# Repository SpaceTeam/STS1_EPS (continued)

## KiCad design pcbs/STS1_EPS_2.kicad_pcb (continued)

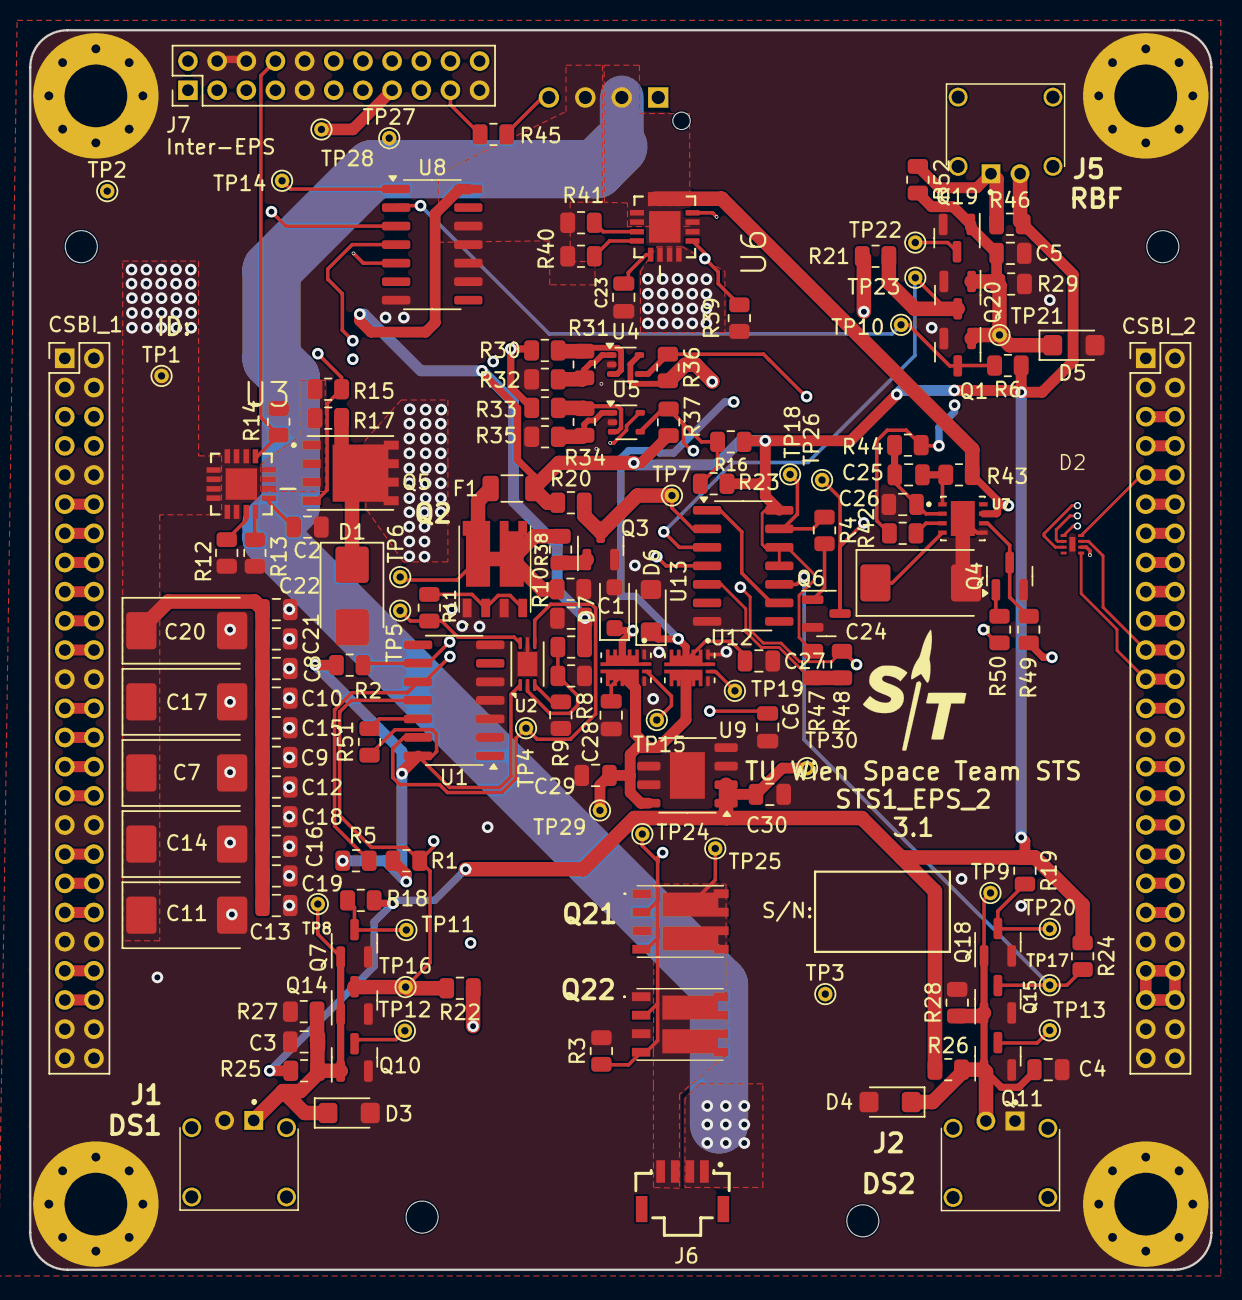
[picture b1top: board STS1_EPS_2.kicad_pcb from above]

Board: 6 copper layers, 81.0 x 85.0 mm, 164 parts (1 on the bottom side), 95 nets.

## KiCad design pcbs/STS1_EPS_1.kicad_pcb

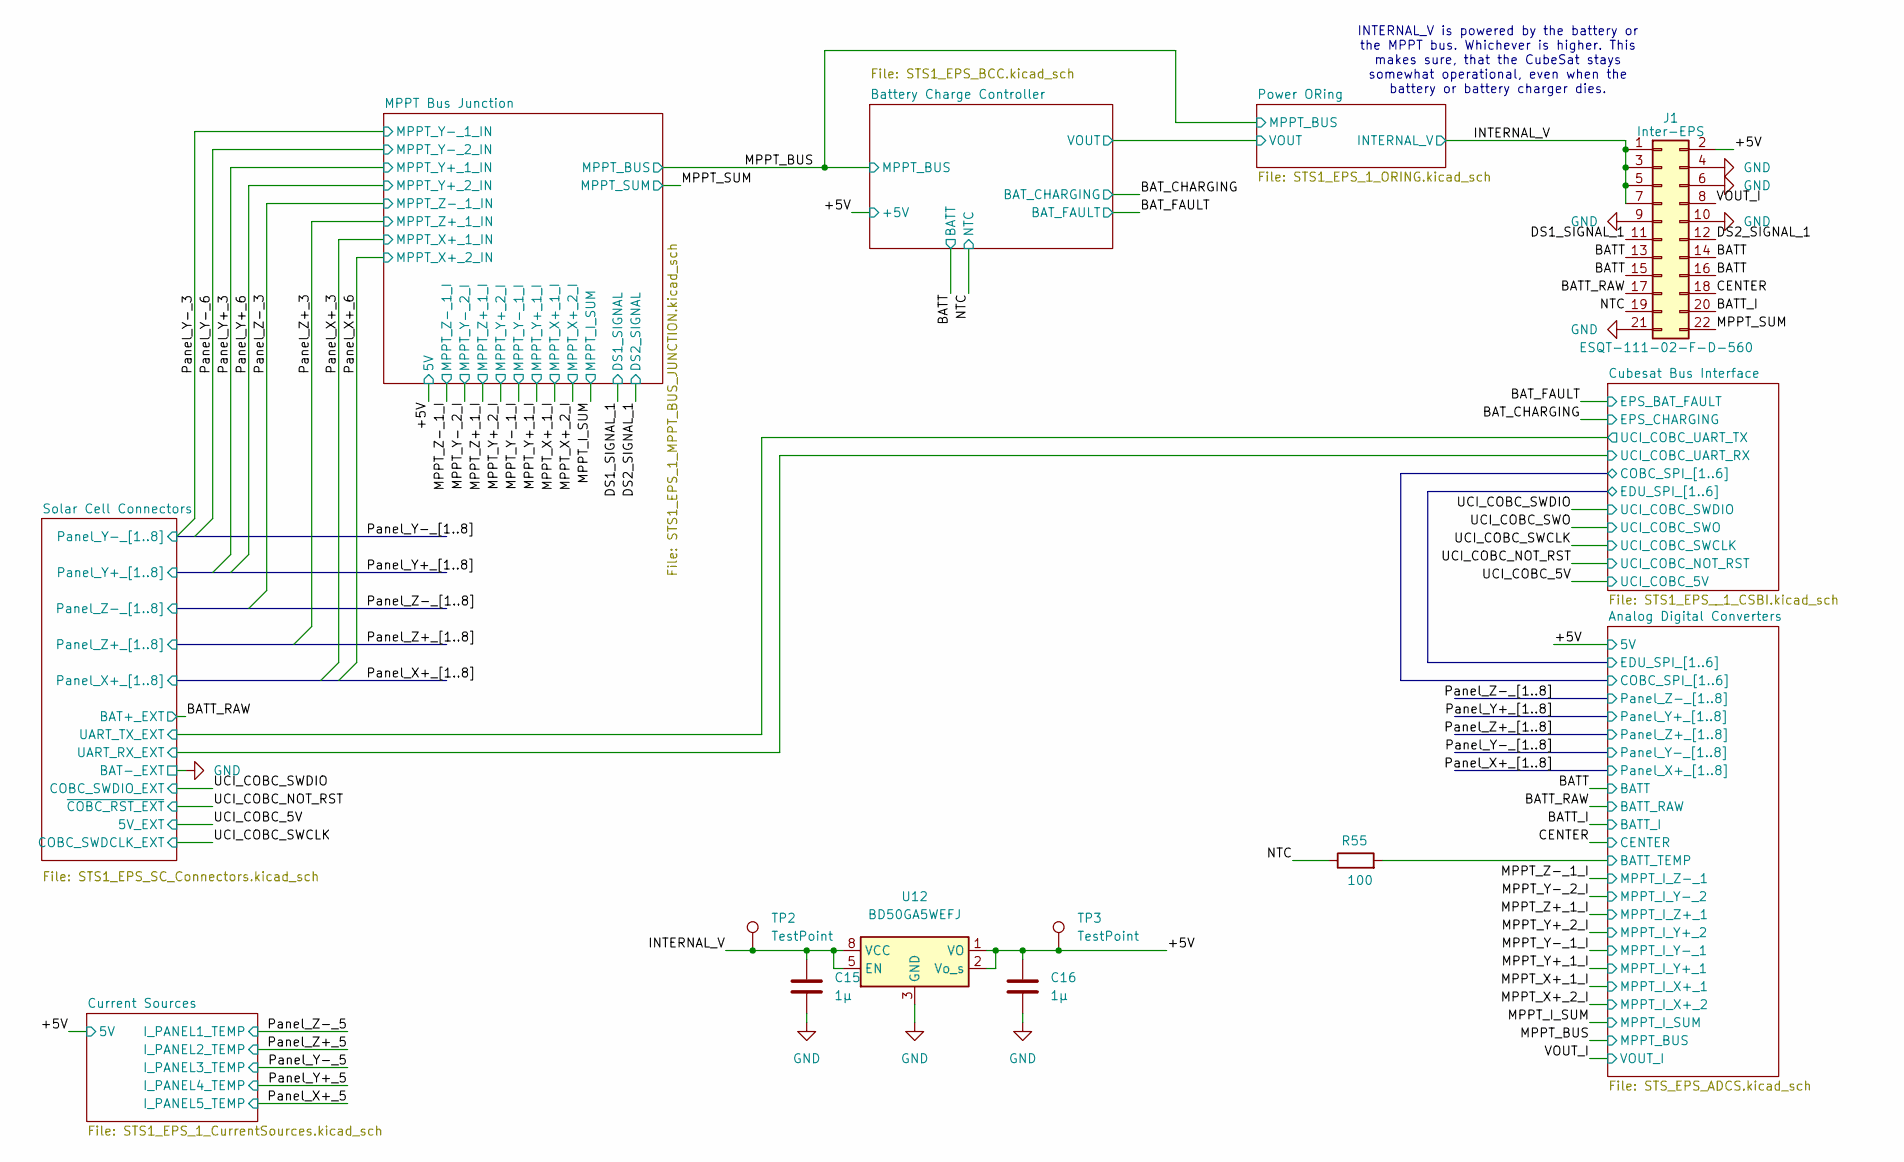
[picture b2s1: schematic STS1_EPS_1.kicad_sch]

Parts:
C15, C16: 1µ; C_0805_2012Metric; Part Nr. C0805T105K4RALTU
J1: Inter-EPS; PinHeader_2x11_P2.00mm_Vertical; Part# ESQT-111-02-F-D-560
R55: 100; R_0805_2012Metric; Part Nr. TNPW0805100RFETA
TP2, TP3: TestPoint; TestPoint_THTPad_D1.0mm_Drill0.5mm
U12: BD50GA5WEFJ; HTSOP-8-1EP_3.9x4.9mm_P1.27mm_EP2.4x3.2mm

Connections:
/+5V: C16.1, J1.2, TP3.1 (1_1), U12.1 (VO), U12.2 (Vo_s); also elsewhere on the board
/Analog Digital Converters/BATT_TEMP: R55.2; also elsewhere on the board
/BATT: J1.13, J1.14, J1.15, J1.16; also elsewhere on the board
/BATT_I: J1.20; also elsewhere on the board
/BATT_RAW: J1.17; also elsewhere on the board
/CENTER: J1.18; also elsewhere on the board
/DS1_SIGNAL_1: J1.11; also elsewhere on the board
/DS2_SIGNAL_1: J1.12; also elsewhere on the board
/INTERNAL_V: C15.1, J1.1, J1.3, J1.5, J1.7, TP2.1 (1_1), U12.5 (EN), U12.8 (VCC); also elsewhere on the board
/NTC: J1.19, R55.1; also elsewhere on the board
/VOUT_I: J1.8; also elsewhere on the board
GND: C15.2, C16.2, J1.4, J1.6, J1.9, J1.10, J1.21, U12.3 (GND), U12.4 (GND), U12.6 (GND), U12.7 (GND), U12.9 (GND); also elsewhere on the board

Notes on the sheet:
INTERNAL_V is powered by the battery or the MPPT bus. Whichever is higher. This makes sure, that the CubeSat stays somewhat operational, even when the battery or battery charger dies.

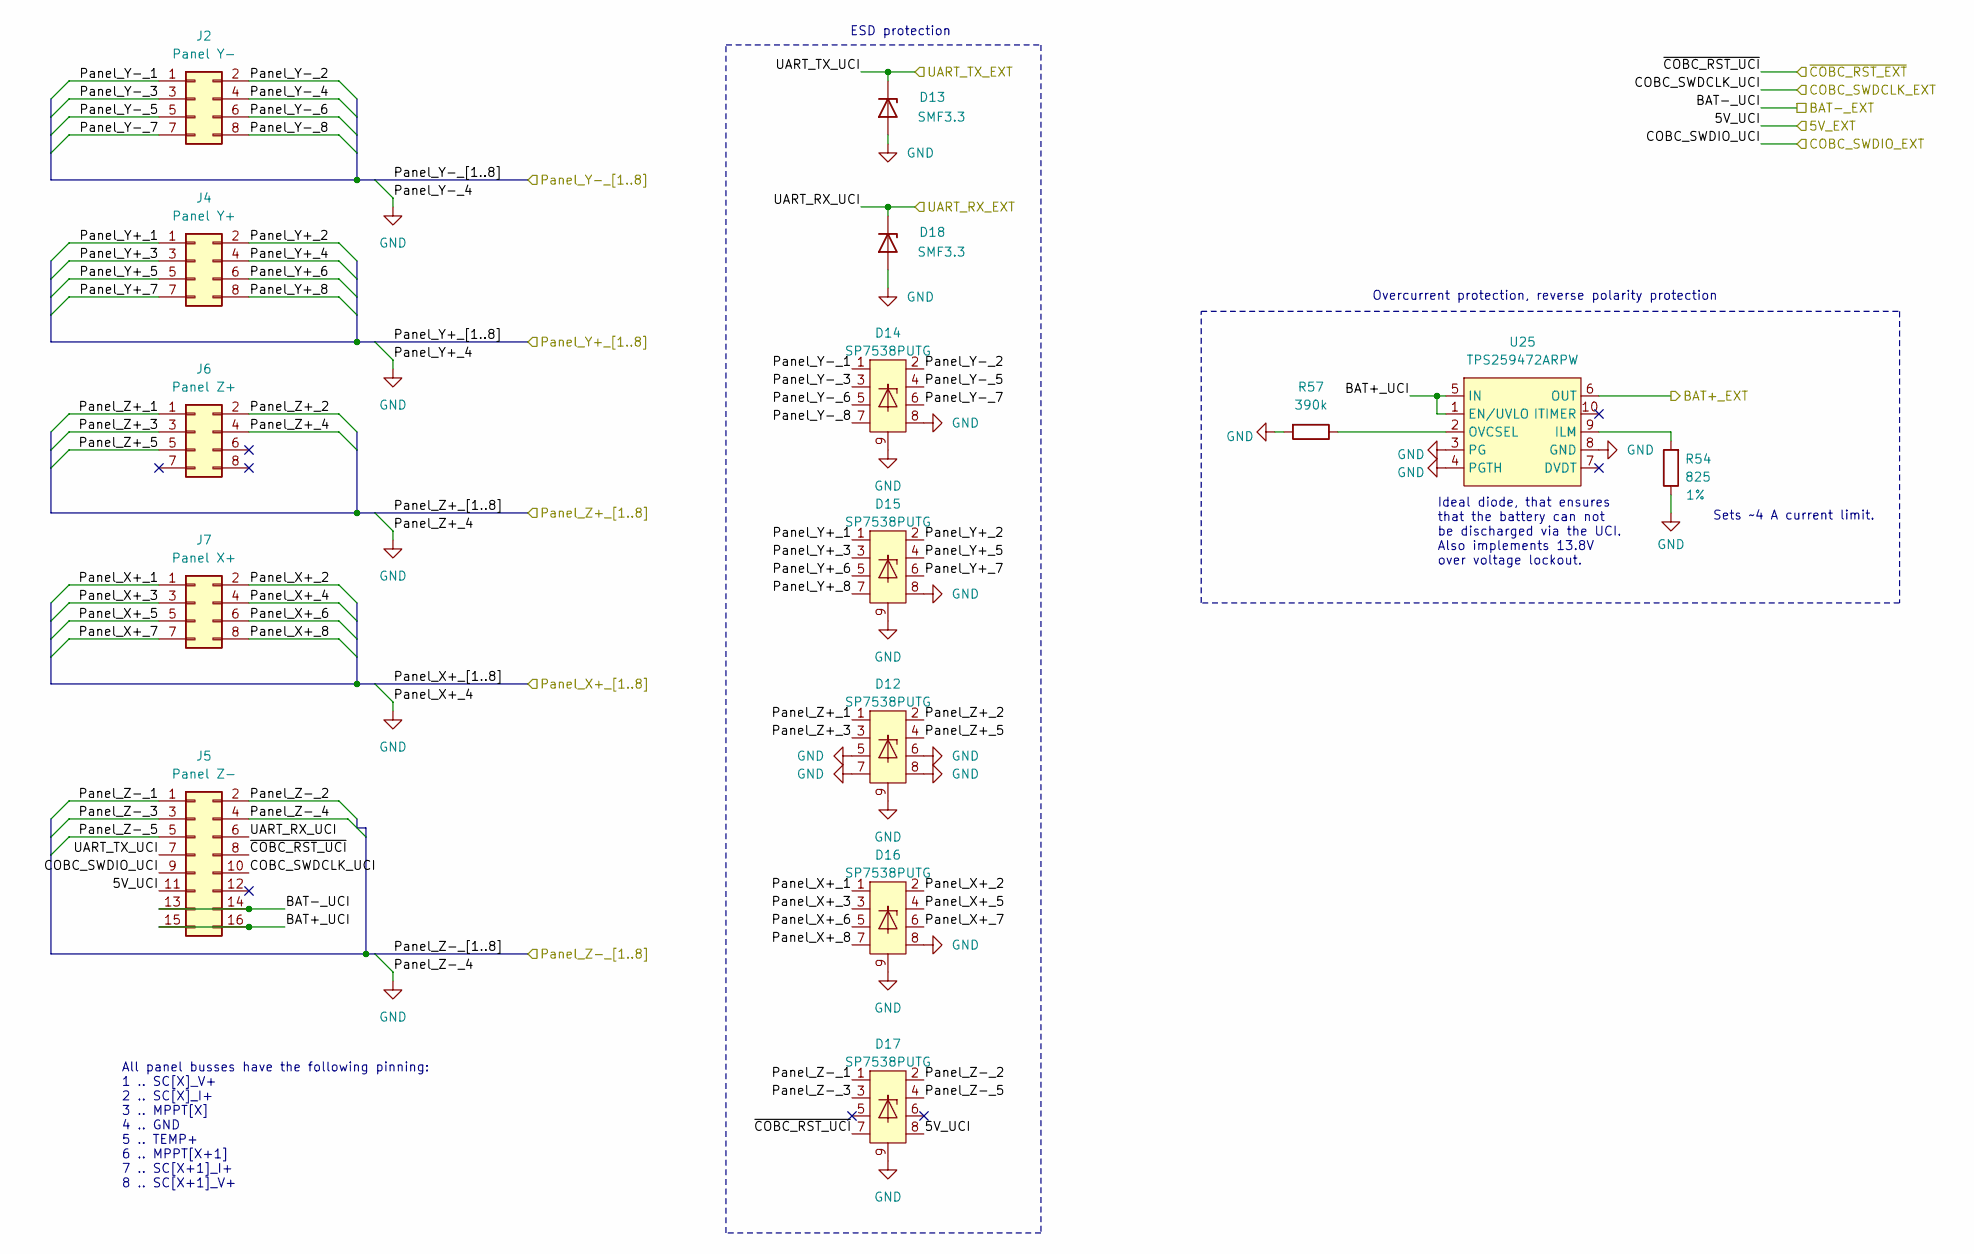
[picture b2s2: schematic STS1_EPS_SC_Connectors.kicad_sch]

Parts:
D12, D14, D15, D16, D17: SP7538PUTG; Diodes_UDFN3810-9_TYPE_B
D13, D18: SMF3.3; D_SOD-123; Part Nr. SMF3.3
J2: Panel Y-; Samtec_T1M-08-X-SV-L_1x08-1MP_P1.0mm_Terminal_Vertical_Latch; Part Nr. SAMTEC_ZF5S-08-03-T-WT
J4: Panel Y+; Samtec_T1M-08-X-SV-L_1x08-1MP_P1.0mm_Terminal_Vertical_Latch; Part Nr. SAMTEC_ZF5S-08-03-T-WT
J5: Panel Z-; Samtec_T1M-16-X-SV-L_1x16-1MP_P1.0mm_Terminal_Vertical_Latch; Part Nr. SAMTEC_ZF5S-08-03-T-WT
J6: Panel Z+; Samtec_T1M-08-X-SV-L_1x08-1MP_P1.0mm_Terminal_Vertical_Latch; Part Nr. SAMTEC_ZF5S-08-03-T-WT
J7: Panel X+; Samtec_T1M-08-X-SV-L_1x08-1MP_P1.0mm_Terminal_Vertical_Latch; Part Nr. SAMTEC_ZF5S-08-03-T-WT
R54: 825; R_0805_2012Metric; Tolerance 1%; Part Nr. RT0805FRE07825RL
R57: 390k; R_0805_2012Metric; Part Nr. RN73R2ATTD3903F25
U25: TPS259472ARPW; TPS259472ARPWR

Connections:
/BATT_RAW: U25.6 (OUT); also elsewhere on the board
/Panel_X+_1: D16.1, J7.1; also elsewhere on the board
/Panel_X+_2: D16.2, J7.2; also elsewhere on the board
/Panel_X+_3: D16.3, J7.3; also elsewhere on the board
/Panel_X+_5: D16.4, J7.5; also elsewhere on the board
/Panel_X+_6: D16.5, J7.6; also elsewhere on the board
/Panel_X+_7: D16.6, J7.7; also elsewhere on the board
/Panel_X+_8: D16.7, J7.8; also elsewhere on the board
/Panel_Y+_1: D15.1, J4.1; also elsewhere on the board
/Panel_Y+_2: D15.2, J4.2; also elsewhere on the board
/Panel_Y+_3: D15.3, J4.3; also elsewhere on the board
/Panel_Y+_5: D15.4, J4.5; also elsewhere on the board
/Panel_Y+_6: D15.5, J4.6; also elsewhere on the board
/Panel_Y+_7: D15.6, J4.7; also elsewhere on the board
/Panel_Y+_8: D15.7, J4.8; also elsewhere on the board
/Panel_Y-_1: D14.1, J2.1; also elsewhere on the board
/Panel_Y-_2: D14.2, J2.2; also elsewhere on the board
/Panel_Y-_3: D14.3, J2.3; also elsewhere on the board
/Panel_Y-_5: D14.4, J2.5; also elsewhere on the board
/Panel_Y-_6: D14.5, J2.6; also elsewhere on the board
/Panel_Y-_7: D14.6, J2.7; also elsewhere on the board
/Panel_Y-_8: D14.7, J2.8; also elsewhere on the board
/Panel_Z+_1: D12.1, J6.1; also elsewhere on the board
/Panel_Z+_2: D12.2, J6.2; also elsewhere on the board
/Panel_Z+_3: D12.3, J6.3; also elsewhere on the board
/Panel_Z+_5: D12.4, J6.5; also elsewhere on the board
/Panel_Z-_1: D17.1, J5.1; also elsewhere on the board
/Panel_Z-_2: D17.2, J5.2; also elsewhere on the board
/Panel_Z-_3: D17.3, J5.3; also elsewhere on the board
/Panel_Z-_5: D17.4, J5.5; also elsewhere on the board
/Solar Cell Connectors/BAT+_UCI: J5.15, J5.16, U25.1 (EN/UVLO), U25.5 (IN)
/Solar Cell Connectors/UART_RX_UCI: D18.1 (K), J5.6; also elsewhere on the board
/Solar Cell Connectors/UART_TX_UCI: D13.1 (K), J5.7; also elsewhere on the board
/UCI_COBC_5V: D17.8, J5.11; also elsewhere on the board
/UCI_COBC_NOT_RST: D17.7, J5.8; also elsewhere on the board
/UCI_COBC_SWCLK: J5.10; also elsewhere on the board
/UCI_COBC_SWDIO: J5.9; also elsewhere on the board
GND: D12.5, D12.6, D12.7, D12.8, D12.9, D13.2 (A), D14.8, D14.9, D15.8, D15.9, D16.8, D16.9, D17.9, D18.2 (A), J2.4, J4.4, J5.4, J5.13, J5.14, J6.4, J7.4, R54.1, R57.2, U25.3 (PG), U25.4 (PGTH), U25.8 (GND); also elsewhere on the board
unnamed: R54.2, U25.9 (ILM)
unnamed: R57.1, U25.2 (OVCSEL)

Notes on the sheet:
ESD protection
Overcurrent protection, reverse polarity protection
Sets ~4 A current limit.
Ideal diode, that ensures that the battery can not be discharged via the UCI. Also implements 13.8V over voltage lockout.
All panel busses have the following pinning: 1 .. SC[X]_V+ 2 .. SC[X]_I+ 3 .. MPPT[X] 4 .. GND 5 .. TEMP+ 6 .. MPPT[X+1] 7 .. SC[X+1]_I+ 8 .. SC[X+1]_V+

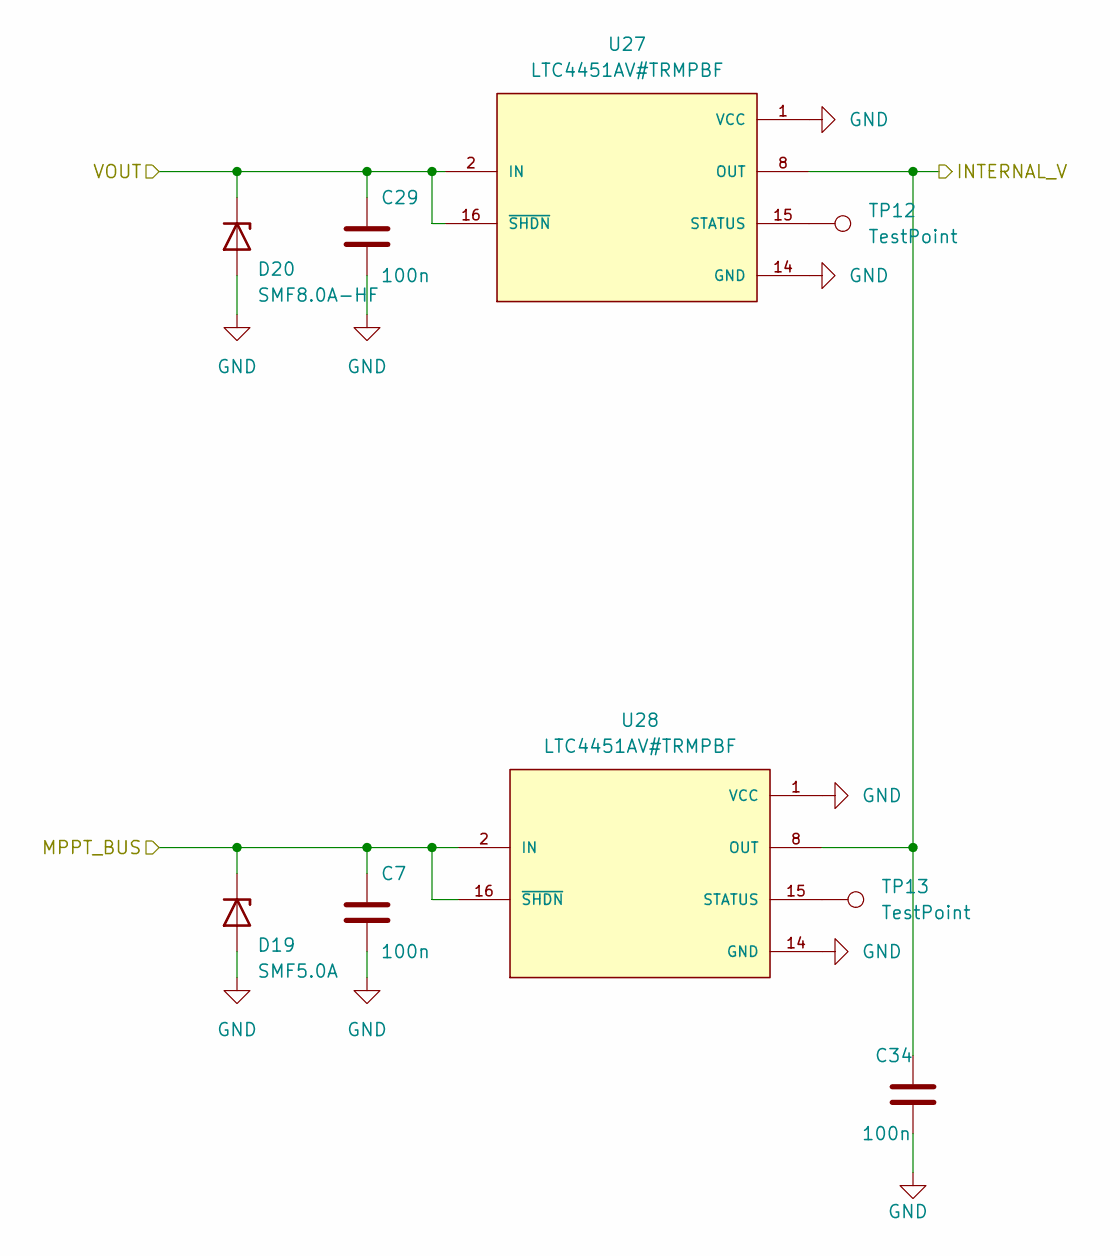
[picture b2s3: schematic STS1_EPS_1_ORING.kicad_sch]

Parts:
C7, C29, C34: 100n; C_0805_2012Metric; Part Nr. C0805T104K1RCLTU
D19: SMF5.0A; D_SMF; Part Nr. SMF5.0A
D20: SMF8.0A-HF; D_SOD-123F; Part Nr. SMF8.0A-HF
TP12, TP13: TestPoint; TestPoint_THTPad_D1.0mm_Drill0.5mm
U27, U28: LTC4451AV#TRMPBF; AD_LQFN-16; PARTREV 0

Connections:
/Battery Charge Controller/VOUT: C29.1, D20.1 (K), U27.2 (IN), U27.16 (~SHDN); also elsewhere on the board
/INTERNAL_V: C34.1, U27.8 (OUT), U28.8 (OUT); also elsewhere on the board
/MPPT_BUS: C7.1, D19.1 (K), U28.2 (IN), U28.16 (~SHDN); also elsewhere on the board
GND: C7.2, C29.2, C34.2, D19.2 (A), D20.2 (A), U27.1 (VCC), U27.14 (GND), U28.1 (VCC), U28.14 (GND); also elsewhere on the board
unnamed: TP12.1 (1_1), U27.15 (STATUS)
unnamed: TP13.1 (1_1), U28.15 (STATUS)

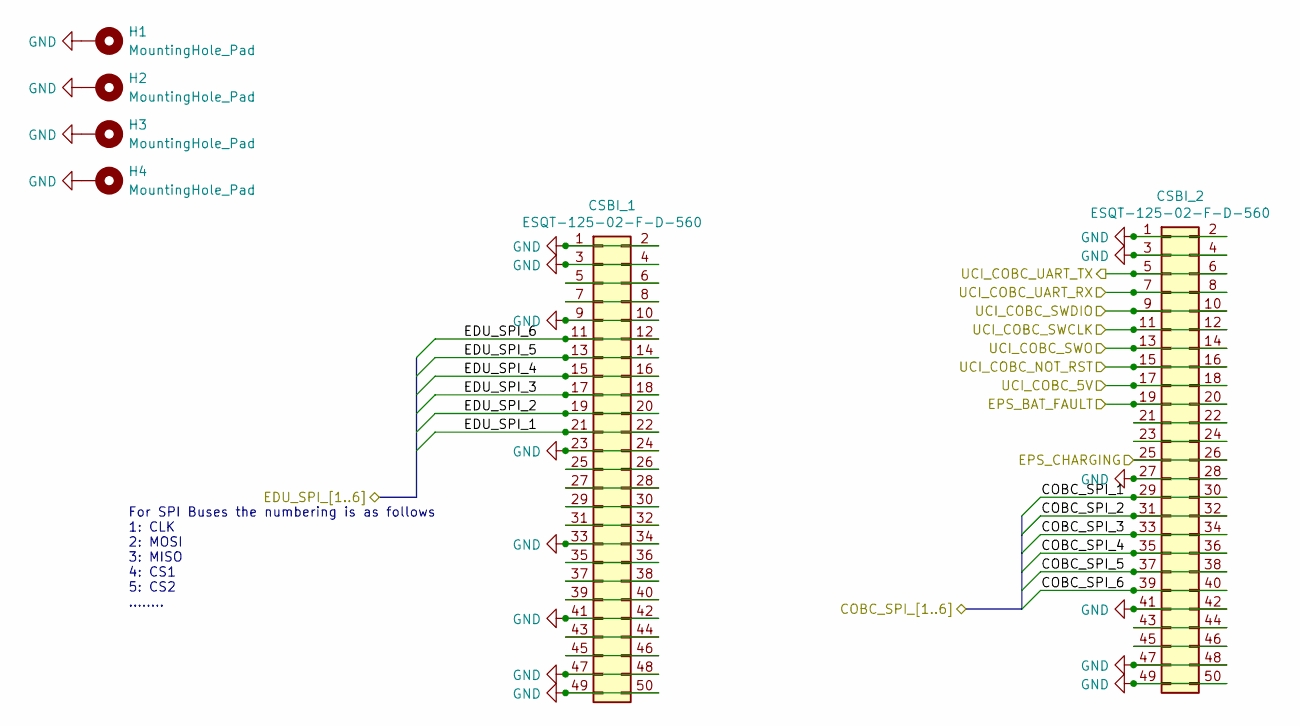
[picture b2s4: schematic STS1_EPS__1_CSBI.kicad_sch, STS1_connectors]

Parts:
CSBI_1, CSBI_2: ESQT-125-02-F-D-560; PinHeader_2x25_P2.00mm_Vertical; Part# ESQT-125-02-F-D-800
H1, H2, H3, H4: MountingHole_Pad; MountingHole_4.3mm_M4_Pad_Via

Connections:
/Analog Digital Converters/COBC_SPI_1: CSBI_2.29, CSBI_2.30; also elsewhere on the board
/Analog Digital Converters/COBC_SPI_2: CSBI_2.31, CSBI_2.32; also elsewhere on the board
/Analog Digital Converters/COBC_SPI_3: CSBI_2.33, CSBI_2.34; also elsewhere on the board
/Analog Digital Converters/COBC_SPI_4: CSBI_2.35, CSBI_2.36; also elsewhere on the board
/Analog Digital Converters/COBC_SPI_5: CSBI_2.37, CSBI_2.38; also elsewhere on the board
/Analog Digital Converters/COBC_SPI_6: CSBI_2.39, CSBI_2.40; also elsewhere on the board
/Analog Digital Converters/EDU_SPI_1: CSBI_1.21, CSBI_1.22; also elsewhere on the board
/Analog Digital Converters/EDU_SPI_2: CSBI_1.19, CSBI_1.20; also elsewhere on the board
/Analog Digital Converters/EDU_SPI_3: CSBI_1.17, CSBI_1.18; also elsewhere on the board
/Analog Digital Converters/EDU_SPI_4: CSBI_1.15, CSBI_1.16; also elsewhere on the board
/Analog Digital Converters/EDU_SPI_5: CSBI_1.13, CSBI_1.14; also elsewhere on the board
/Analog Digital Converters/EDU_SPI_6: CSBI_1.11, CSBI_1.12; also elsewhere on the board
/BAT_CHARGING: CSBI_2.25, CSBI_2.26; also elsewhere on the board
/BAT_FAULT: CSBI_2.19, CSBI_2.20; also elsewhere on the board
/Solar Cell Connectors/UART_RX_UCI: CSBI_2.7, CSBI_2.8; also elsewhere on the board
/Solar Cell Connectors/UART_TX_UCI: CSBI_2.5, CSBI_2.6; also elsewhere on the board
/UCI_COBC_5V: CSBI_2.17, CSBI_2.18; also elsewhere on the board
/UCI_COBC_NOT_RST: CSBI_2.15, CSBI_2.16; also elsewhere on the board
/UCI_COBC_SWCLK: CSBI_2.11, CSBI_2.12; also elsewhere on the board
/UCI_COBC_SWDIO: CSBI_2.9, CSBI_2.10; also elsewhere on the board
/UCI_COBC_SWO: CSBI_2.13, CSBI_2.14
GND: CSBI_1.1, CSBI_1.2, CSBI_1.3, CSBI_1.4, CSBI_1.9, CSBI_1.10, CSBI_1.23, CSBI_1.24, CSBI_1.33, CSBI_1.34, CSBI_1.41, CSBI_1.42, CSBI_1.47, CSBI_1.48, CSBI_1.49, CSBI_1.50, CSBI_2.1, CSBI_2.2, CSBI_2.3, CSBI_2.4, CSBI_2.27, CSBI_2.28, CSBI_2.41, CSBI_2.42, CSBI_2.47, CSBI_2.48, CSBI_2.49, CSBI_2.50, H1.1 (1_1), H2.1 (1_1), H3.1 (1_1), H4.1 (1_1); also elsewhere on the board
unnamed: CSBI_1.5, CSBI_1.6
unnamed: CSBI_1.7, CSBI_1.8
unnamed: CSBI_1.25, CSBI_1.26
unnamed: CSBI_1.27, CSBI_1.28
unnamed: CSBI_1.29, CSBI_1.30
unnamed: CSBI_1.31, CSBI_1.32
unnamed: CSBI_1.35, CSBI_1.36
unnamed: CSBI_1.37, CSBI_1.38
unnamed: CSBI_1.39, CSBI_1.40
unnamed: CSBI_1.43, CSBI_1.44
unnamed: CSBI_1.45, CSBI_1.46
unnamed: CSBI_2.21, CSBI_2.22
unnamed: CSBI_2.23, CSBI_2.24
unnamed: CSBI_2.43, CSBI_2.44
unnamed: CSBI_2.45, CSBI_2.46

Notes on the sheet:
For SPI Buses the numbering is as follows 1: CLK 2: MOSI 3: MISO 4: CS1 5: CS2 ........

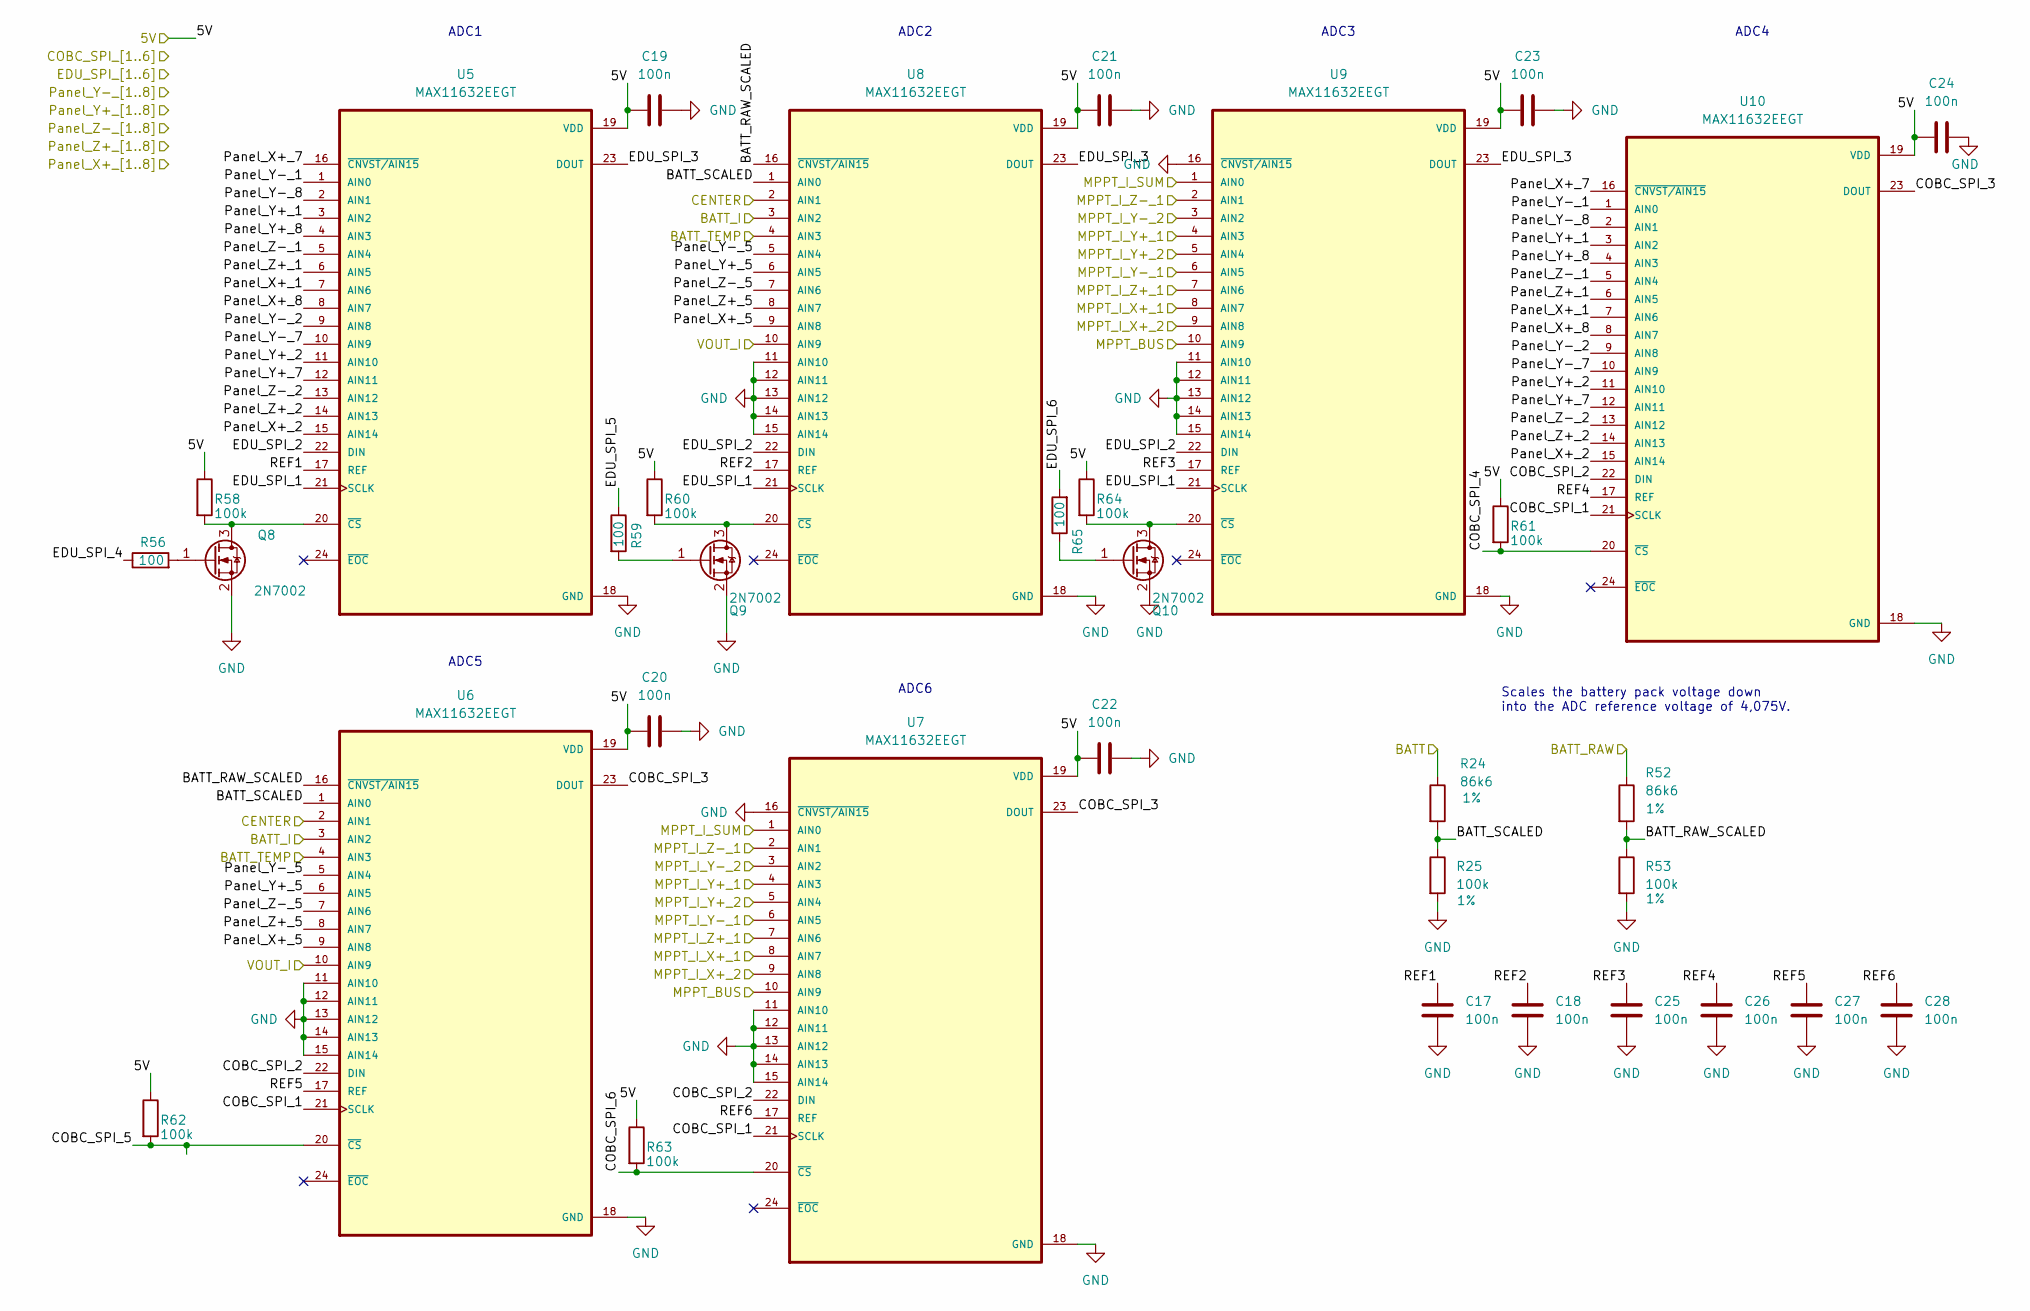
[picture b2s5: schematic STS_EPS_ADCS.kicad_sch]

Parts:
C17, C18, C19, C20, C21, C22, C23, C24, C25, C26, C27, C28: 100n; C_0805_2012Metric; Part Nr. C0805T104K1RCLTU
Q8, Q9, Q10: 2N7002; SOT-23; Part Nr. 2N7002
R24, R52: 86k6; R_0805_2012Metric; Tolerance 1%; Part Nr. RCA080586K6FKEA
R25, R53: 100k; R_0805_2012Metric; Tolerance 1%; Part Nr. TNPW0805100KFEEA
R56, R59, R65: 100; R_0805_2012Metric; Part Nr. TNPW0805100RFETA
R58, R60, R61, R62, R63, R64: 100k; R_0805_2012Metric; Part Nr. TNPW0805100KFEEA
U5, U6, U7, U8, U9, U10: MAX11632EEGT; MAX_QSOP24

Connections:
/+5V: C19.1, C20.1, C21.1, C22.1, C23.1, C24.1, R58.1, R60.1, R61.1, R62.1, R63.1, R64.1, U5.19 (VDD), U6.19 (VDD), U7.19 (VDD), U8.19 (VDD), U9.19 (VDD), U10.19 (VDD); also elsewhere on the board
/Analog Digital Converters/BATT_RAW_SCALED: R52.2, R53.1, U6.16 (~CNVST/AIN15), U8.16 (~CNVST/AIN15)
/Analog Digital Converters/BATT_SCALED: R24.2, R25.1, U6.1 (AIN0), U8.1 (AIN0)
/Analog Digital Converters/BATT_TEMP: U6.4 (AIN3), U8.4 (AIN3); also elsewhere on the board
/Analog Digital Converters/COBC_SPI_1: U6.21 (SCLK), U7.21 (SCLK), U10.21 (SCLK); also elsewhere on the board
/Analog Digital Converters/COBC_SPI_2: U6.22 (DIN), U7.22 (DIN), U10.22 (DIN); also elsewhere on the board
/Analog Digital Converters/COBC_SPI_3: U6.23 (DOUT), U7.23 (DOUT), U10.23 (DOUT); also elsewhere on the board
/Analog Digital Converters/COBC_SPI_4: R61.2, U10.20 (~CS); also elsewhere on the board
/Analog Digital Converters/COBC_SPI_5: R62.2, U6.20 (~CS); also elsewhere on the board
/Analog Digital Converters/COBC_SPI_6: R63.2, U7.20 (~CS); also elsewhere on the board
/Analog Digital Converters/EDU_SPI_1: U5.21 (SCLK), U8.21 (SCLK), U9.21 (SCLK); also elsewhere on the board
/Analog Digital Converters/EDU_SPI_2: U5.22 (DIN), U8.22 (DIN), U9.22 (DIN); also elsewhere on the board
/Analog Digital Converters/EDU_SPI_3: U5.23 (DOUT), U8.23 (DOUT), U9.23 (DOUT); also elsewhere on the board
/Analog Digital Converters/EDU_SPI_4: R56.1; also elsewhere on the board
/Analog Digital Converters/EDU_SPI_5: R59.1; also elsewhere on the board
/Analog Digital Converters/EDU_SPI_6: R65.2; also elsewhere on the board
/Analog Digital Converters/REF1: C17.2, U5.17 (REF)
/Analog Digital Converters/REF2: C18.2, U8.17 (REF)
/Analog Digital Converters/REF3: C25.2, U9.17 (REF)
/Analog Digital Converters/REF4: C26.2, U10.17 (REF)
/Analog Digital Converters/REF5: C27.2, U6.17 (REF)
/Analog Digital Converters/REF6: C28.2, U7.17 (REF)
/BATT: R24.1; also elsewhere on the board
/BATT_I: U6.3 (AIN2), U8.3 (AIN2); also elsewhere on the board
/BATT_RAW: R52.1; also elsewhere on the board
/CENTER: U6.2 (AIN1), U8.2 (AIN1); also elsewhere on the board
/MPPT_BUS: U7.10 (AIN9), U9.10 (AIN9); also elsewhere on the board
/MPPT_I_SUM: U7.1 (AIN0), U9.1 (AIN0); also elsewhere on the board
/MPPT_X+_1_I: U7.8 (AIN7), U9.8 (AIN7); also elsewhere on the board
/MPPT_X+_2_I: U7.9 (AIN8), U9.9 (AIN8); also elsewhere on the board
/MPPT_Y+_1_I: U7.4 (AIN3), U9.4 (AIN3); also elsewhere on the board
/MPPT_Y+_2_I: U7.5 (AIN4), U9.5 (AIN4); also elsewhere on the board
/MPPT_Y-_1_I: U7.6 (AIN5), U9.6 (AIN5); also elsewhere on the board
/MPPT_Y-_2_I: U7.3 (AIN2), U9.3 (AIN2); also elsewhere on the board
/MPPT_Z+_1_I: U7.7 (AIN6), U9.7 (AIN6); also elsewhere on the board
/MPPT_Z-_1_I: U7.2 (AIN1), U9.2 (AIN1); also elsewhere on the board
/Panel_X+_1: U5.7 (AIN6), U10.7 (AIN6); also elsewhere on the board
/Panel_X+_2: U5.15 (AIN14), U10.15 (AIN14); also elsewhere on the board
/Panel_X+_5: U6.9 (AIN8), U8.9 (AIN8); also elsewhere on the board
/Panel_X+_7: U5.16 (~CNVST/AIN15), U10.16 (~CNVST/AIN15); also elsewhere on the board
/Panel_X+_8: U5.8 (AIN7), U10.8 (AIN7); also elsewhere on the board
/Panel_Y+_1: U5.3 (AIN2), U10.3 (AIN2); also elsewhere on the board
/Panel_Y+_2: U5.11 (AIN10), U10.11 (AIN10); also elsewhere on the board
/Panel_Y+_5: U6.6 (AIN5), U8.6 (AIN5); also elsewhere on the board
/Panel_Y+_7: U5.12 (AIN11), U10.12 (AIN11); also elsewhere on the board
/Panel_Y+_8: U5.4 (AIN3), U10.4 (AIN3); also elsewhere on the board
/Panel_Y-_1: U5.1 (AIN0), U10.1 (AIN0); also elsewhere on the board
/Panel_Y-_2: U5.9 (AIN8), U10.9 (AIN8); also elsewhere on the board
/Panel_Y-_5: U6.5 (AIN4), U8.5 (AIN4); also elsewhere on the board
/Panel_Y-_7: U5.10 (AIN9), U10.10 (AIN9); also elsewhere on the board
/Panel_Y-_8: U5.2 (AIN1), U10.2 (AIN1); also elsewhere on the board
/Panel_Z+_1: U5.6 (AIN5), U10.6 (AIN5); also elsewhere on the board
/Panel_Z+_2: U5.14 (AIN13), U10.14 (AIN13); also elsewhere on the board
/Panel_Z+_5: U6.8 (AIN7), U8.8 (AIN7); also elsewhere on the board
/Panel_Z-_1: U5.5 (AIN4), U10.5 (AIN4); also elsewhere on the board
/Panel_Z-_2: U5.13 (AIN12), U10.13 (AIN12); also elsewhere on the board
/Panel_Z-_5: U6.7 (AIN6), U8.7 (AIN6); also elsewhere on the board
/VOUT_I: U6.10 (AIN9), U8.10 (AIN9); also elsewhere on the board
GND: C17.1, C18.1, C19.2, C20.2, C21.2, C22.2, C23.2, C24.2, C25.1, C26.1, C27.1, C28.1, Q8.2 (S), Q9.2 (S), Q10.2 (S), R25.2, R53.2, U5.18 (GND), U6.11 (AIN10), U6.12 (AIN11), U6.13 (AIN12), U6.14 (AIN13), U6.15 (AIN14), U6.18 (GND), U7.11 (AIN10), U7.12 (AIN11), U7.13 (AIN12), U7.14 (AIN13), U7.15 (AIN14), U7.16 (~CNVST/AIN15), U7.18 (GND), U8.11 (AIN10), U8.12 (AIN11), U8.13 (AIN12), U8.14 (AIN13), U8.15 (AIN14), U8.18 (GND), U9.11 (AIN10), U9.12 (AIN11), U9.13 (AIN12), U9.14 (AIN13), U9.15 (AIN14), U9.16 (~CNVST/AIN15), U9.18 (GND), U10.18 (GND); also elsewhere on the board
unnamed: Q8.3 (D), R58.2, U5.20 (~CS)
unnamed: Q8.1 (G), R56.2
unnamed: Q9.3 (D), R60.2, U8.20 (~CS)
unnamed: Q9.1 (G), R59.2
unnamed: Q10.3 (D), R64.2, U9.20 (~CS)
unnamed: Q10.1 (G), R65.1

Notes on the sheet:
ADC5
ADC4
ADC6
ADC2
Scales the battery pack voltage down into the ADC reference voltage of 4,075V.
ADC3
ADC1
